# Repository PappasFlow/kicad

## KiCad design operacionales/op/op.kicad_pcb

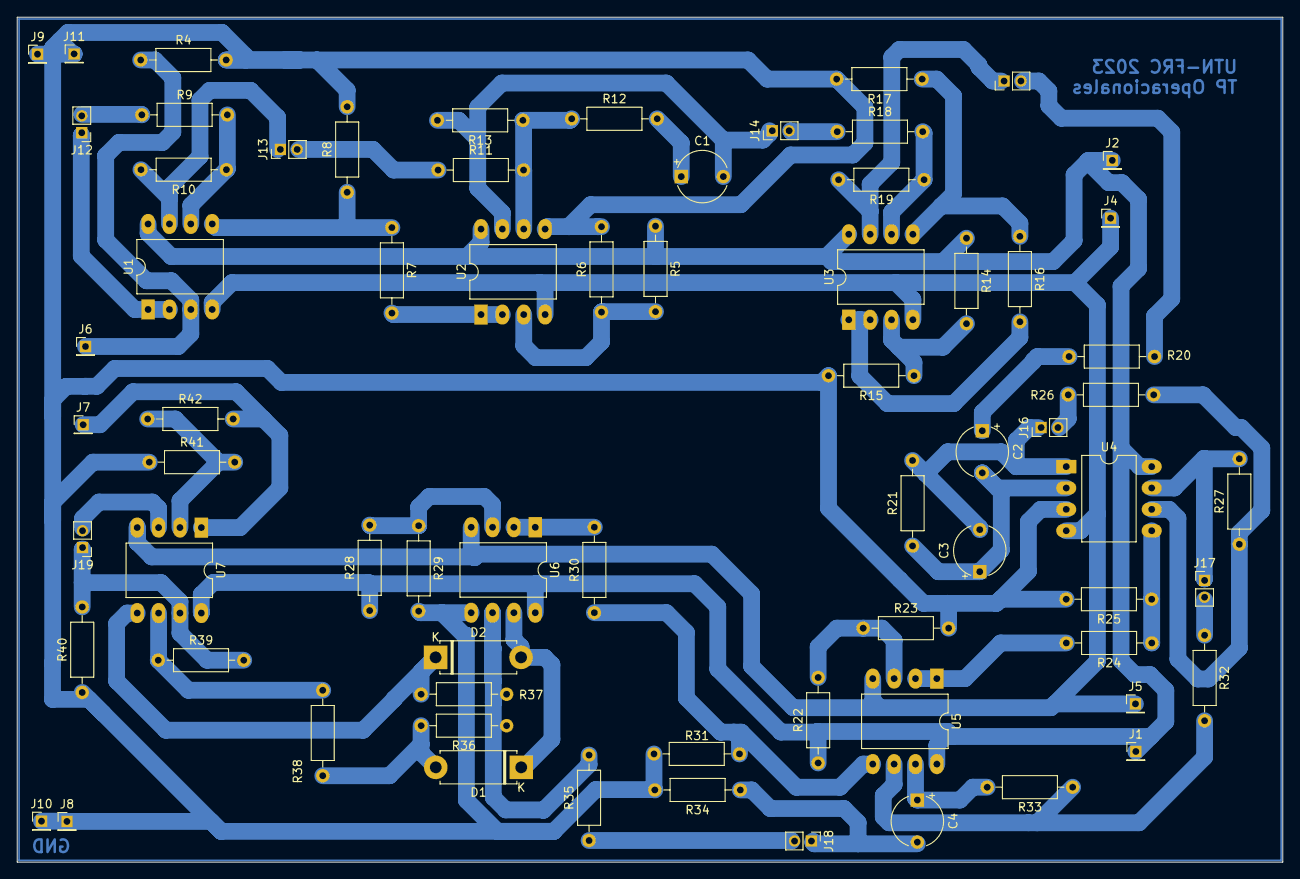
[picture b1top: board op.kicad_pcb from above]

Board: 2 copper layers, 150.4 x 100.4 mm, 70 parts (0 on the bottom side), 48 nets.

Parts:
C1: 12nF; CP_Radial_Tantal_D6.0mm_P5.00mm
C2: 1nF; CP_Radial_Tantal_D6.0mm_P5.00mm
C3: 56pF; CP_Radial_Tantal_D6.0mm_P5.00mm
C4: 10nF; CP_Radial_Tantal_D6.0mm_P5.00mm
D1, D2: 1N914; D_5W_P10.16mm_Horizontal
J1, J2, J4, J5, J6, J7, J8, J9, J10, J11: Conn_01x01_Pin; PinHeader_1x01_P2.00mm_Vertical
J12, J13, J14, J15, J16, J17, J18, J19: Conn_01x02; PinHeader_1x02_P2.00mm_Vertical
R4: 15k; R_Axial_DIN0207_L6.3mm_D2.5mm_P10.16mm_Horizontal
R5: 18k; R_Axial_DIN0207_L6.3mm_D2.5mm_P10.16mm_Horizontal
R6, R15, R23, R29: 2k; R_Axial_DIN0207_L6.3mm_D2.5mm_P10.16mm_Horizontal
R7, R8, R9, R10, R13, R24, R25, R26, R30, R31, R35, R36, R37, R38, R39, R40, R41, R42: 100k; R_Axial_DIN0207_L6.3mm_D2.5mm_P10.16mm_Horizontal
R11, R16, R18: 10k; R_Axial_DIN0207_L6.3mm_D2.5mm_P10.16mm_Horizontal
R12: 100; R_Axial_DIN0207_L6.3mm_D2.5mm_P10.16mm_Horizontal
R14: 12k; R_Axial_DIN0207_L6.3mm_D2.5mm_P10.16mm_Horizontal
R17, R19: 47k; R_Axial_DIN0207_L6.3mm_D2.5mm_P10.16mm_Horizontal
R20: 4.7K; R_Axial_DIN0207_L6.3mm_D2.5mm_P10.16mm_Horizontal
R21: 63k; R_Axial_DIN0207_L6.3mm_D2.5mm_P10.16mm_Horizontal
R22, R28: 13k; R_Axial_DIN0207_L6.3mm_D2.5mm_P10.16mm_Horizontal
R27: 50k; R_Axial_DIN0207_L6.3mm_D2.5mm_P10.16mm_Horizontal
R32: 56k; R_Axial_DIN0207_L6.3mm_D2.5mm_P10.16mm_Horizontal
R33: 42k; R_Axial_DIN0207_L6.3mm_D2.5mm_P10.16mm_Horizontal
R34: 470; R_Axial_DIN0207_L6.3mm_D2.5mm_P10.16mm_Horizontal
U1, U2, U3, U4, U5, U6, U7: TL082; DIP-8_W10.16mm_LongPads

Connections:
+15V: J1.1, J2.1, R5.1, R14.1, R22.1, R28.1, U1.8 (V+), U2.8 (V+), U3.8 (V+), U4.8 (V+), U5.8 (V+), U6.8 (V+), U7.8 (V+)
-15V: J4.1, J5.1, U1.4 (V-), U2.4 (V-), U3.4 (V-), U4.4 (V-), U5.4 (V-), U6.4 (V-), U7.4 (V-)
GND: J8.1, J9.1, J10.1, J11.1, R4.2, R6.2, R8.2, R15.2, R17.2, R23.2, R25.2, R29.2, R31.2, R34.2, R40.1, R41.1, U2.5 (+), U4.3 (+), U6.5 (+)
INPUT: J6.1, R4.1, U1.3 (+)
unnamed: C1.1, R12.2
unnamed: C2.1, R20.2
unnamed: C4.1, R33.2, U5.7
unnamed: D1.2 (A), R36.2, R38.1
unnamed: D1.1 (K), D2.2 (A), U6.7
unnamed: D2.1 (K), R37.2, U7.5 (+)
unnamed: J12.1, U1.1, U1.2 (-)
unnamed: J13.1, R10.2, U1.7
unnamed: C1.2, J14.1, R13.2, U2.7
unnamed: J15.1, R19.2, U3.7
unnamed: C3.2, J16.1, R21.2, U4.1
unnamed: J17.1, R27.2, U4.7
unnamed: C4.2, J18.1, R34.1
unnamed: J19.1, R39.2, R40.2, U7.7
unnamed: R7.1, R8.1, U1.5 (+)
unnamed: R9.2, R10.1, U1.6 (-)
unnamed: R5.2, R6.1, U2.3 (+)
unnamed: R7.2, U2.1, U2.2 (-)
unnamed: R11.2, R12.1, R13.1, U2.6 (-)
unnamed: R14.2, R15.1, U3.3 (+)
unnamed: R16.2, U3.1, U3.2 (-)
unnamed: R16.1, R17.1, U3.5 (+)
unnamed: R18.2, R19.1, U3.6 (-)
unnamed: C2.2, C3.1, R21.1, U4.2 (-)
unnamed: R24.1, R25.1, U4.5 (+)
unnamed: R26.2, R27.1, U4.6 (-)
unnamed: R22.2, R23.1, U5.3 (+)
unnamed: R24.2, U5.1, U5.2 (-)
unnamed: R30.1, R31.1, U5.5 (+)
unnamed: R32.2, R33.1, U5.6 (-)
unnamed: R28.2, R29.1, U6.3 (+)
unnamed: R30.2, U6.1, U6.2 (-)
unnamed: R35.2, R36.1, R37.1, U6.6 (-)
unnamed: R41.2, R42.1, U7.2 (-)
unnamed: R38.2, R39.1, U7.6 (-)
out: J7.1, R42.2, U7.1
out_E1: J12.2, R9.1
out_E2: J13.2, R11.1
out_E3: J14.2, R18.1
out_E4: J15.2, R20.1
out_E5: J16.2, R26.1
out_E6: J17.2, R32.1
out_E7: J18.2, R35.1
out_E8: J19.2, U7.3 (+)

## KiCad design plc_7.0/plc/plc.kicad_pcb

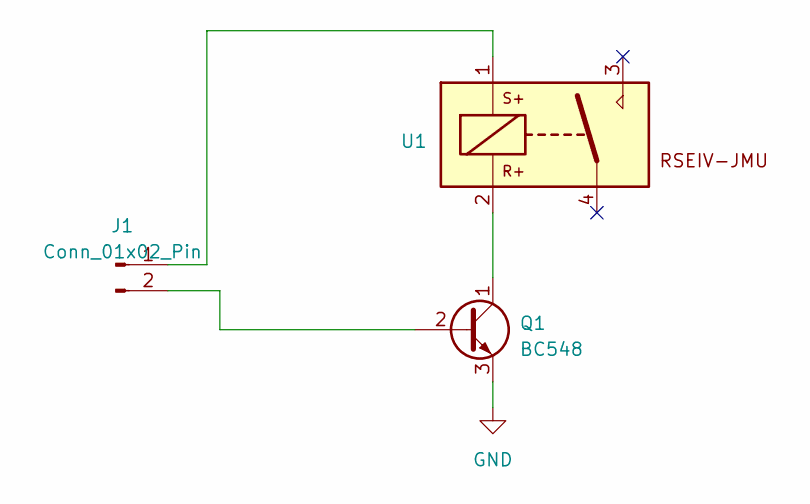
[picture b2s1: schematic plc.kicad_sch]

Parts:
J1: Conn_01x02_Pin; TerminalBlock_Altech_AK300-2_P5.00mm
Q1: BC548; TO-92_Inline
U1: RSEIV-JMU

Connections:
GND: Q1.3 (E)
unnamed: J1.1, U1.1
unnamed: J1.2, Q1.2 (B)
unnamed: Q1.1 (C), U1.2

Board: 2 copper layers, 3 parts (0 on the bottom side), 3 nets, no tracks yet.
